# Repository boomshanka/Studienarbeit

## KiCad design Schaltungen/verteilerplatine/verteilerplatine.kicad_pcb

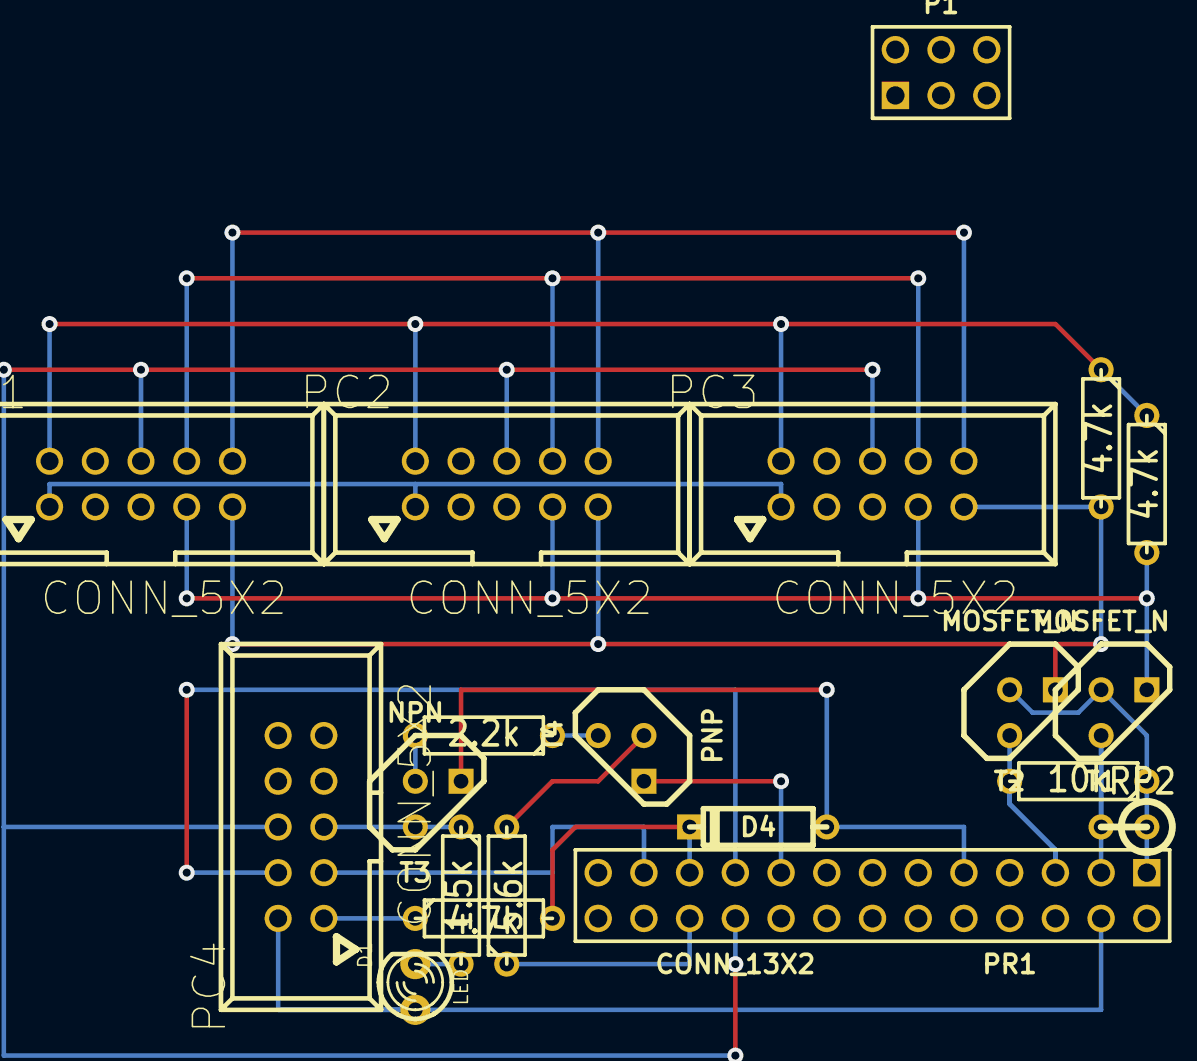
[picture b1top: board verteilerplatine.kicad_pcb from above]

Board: 2 copper layers, 20 parts (0 on the bottom side), 20 nets.

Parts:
D1: LED; LED-3MM
D4: 3.3V; D3
P1: DIN_5; pin_array_3x2
PC1, PC2, PC3, PC4: CONN_5X2; VASCH5x2
PR1: CONN_13X2; pin_array_13x2
R1: 2.2k; R3
R2: 5.6k; R3
R3: 4.7k; R3
RD1: 1.5k; R3
RP1: 10k; R3
RP2: 10k; R1
RP3, RP4: 4.7k; R3
T1, T2: MOSFET_N; TO92DGS
T3: NPN; TO92
T4: PNP; TO92

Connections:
+3.3V: PR1.1, PR1.17, RP1.1, RP2.1, T1.G, T2.G, T4.1
+5V: D1.1, P1.1, PC1.2, PC2.2, PC3.2, PC4.2, PR1.2, PR1.4, RP3.1, RP4.1
+12V: P1.2, PC1.8, PC2.8, PC3.8
-12V: P1.4, PC1.10, PC2.10, PC3.10
/Mikrocontroller/MISO: PC4.1, R3.1
/Mikrocontroller/MOSI: PC4.4, PR1.19
/Mikrocontroller/Reset: PC4.5, RD1.1, T3.3
/Mikrocontroller/SCK: PC4.3, PR1.23
/Mikrocontroller/SCL: PC1.9, PC2.9, PC3.9, RP3.2, T2.D
/Mikrocontroller/SDA: PC1.7, PC2.7, PC3.7, RP4.2, T1.D
/RaspberryPI/MISO: D4.2, PR1.21, R3.2
/RaspberryPI/Reset: PR1.22, R2.1
/RaspberryPI/SCL: PR1.5, RP1.2, T2.S
/RaspberryPI/SDA: PR1.3, RP2.2, T1.S
GND: D4.1, P1.3, PC1.6, PC2.6, PC3.6, PC4.6, PR1.6, PR1.9, PR1.14, PR1.20, PR1.25, T3.1
unnamed: R2.2, T4.2
unnamed: R1.1, T4.3
unnamed: R1.2, T3.2
unnamed: PC1.1, PC2.1, PC3.1
unnamed: D1.2, RD1.2

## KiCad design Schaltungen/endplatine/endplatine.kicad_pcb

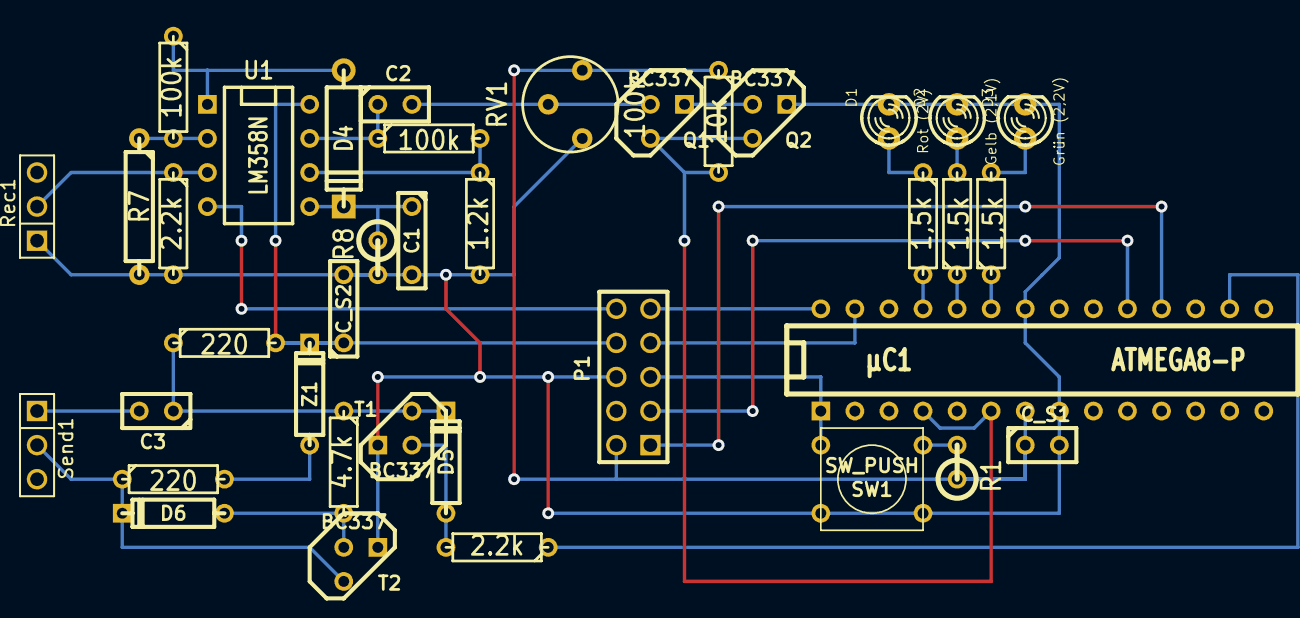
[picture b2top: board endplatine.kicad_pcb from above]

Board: 2 copper layers, 38 parts (0 on the bottom side), 32 nets.

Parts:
C1: 100p; C2
C2: 10n; C1
C3: 100n; C1
C_S1: 100n; C1
C_S2: 100n; C2
D1: Rot (2V); LED-3MM
D2: Gelb (2,1V); LED-3MM
D3: Grün (2,2V); LED-3MM
D4: DIODE; D4
D5, D6: DIODE; D3
P1: CONN_5X2; PIN_ARRAY_5x2
Q1, Q2: BC337; TO92-EBC
R1: 10k; R1
R2, R3, R4: 1,5k; R3
R5: 2.2k; R3
R6, R9: 100k; R3
R7: 1.2k; R4
R8: 560k; R1
R10: 1.2k; R3
R11: 10k; R3
R12, R13: 220; R3
RB1: 2.2k; R3
RB2: 4.7k; R3
RV1: 100k; RV2
Rec1: 2.55nF; PIN_ARRAY_3X1
SW1: SW_PUSH; SW_PUSH_SMALL
Send1: 2,55n; PIN_ARRAY_3X1
T1, T2: BC337; TO92-EBC
U1: LM358N; DIP-8__300
Z1: 3.9V; D3
µC1: ATMEGA8-P; DIP-28__300

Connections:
+5V: C_S1.1, P1.2, R1.1, R11.1, RV1.3, µC1.7
+12V: C_S2.1, P1.8, R12.2, U1.8, Z1.2
-12V: P1.10, U1.4
/Mikrocontroller/Empfänger/Signal: Q1.C, Q2.C, R11.2, µC1.4, µC1.6
/Mikrocontroller/Sender/40kHz PWM: RB1.1, µC1.16
GND: C1.2, C_S1.2, C_S2.2, D1.2, D2.2, D3.2, P1.6, Q2.E, R5.2, R7.2, R8.2, R10.2, RV1.1, Rec1.1, SW1.1, T1.E, T2.E, µC1.8, µC1.22
MISO: P1.1, µC1.18
MOSI: P1.4, µC1.17
unnamed: R3.1, µC1.24
unnamed: R4.2, µC1.25
unnamed: D3.1, R2.2
unnamed: D2.1, R3.2
unnamed: D1.1, R4.1
unnamed: R2.1, µC1.23
unnamed: C3.2, Send1.1
unnamed: R13.2, Z1.1
unnamed: C3.1, D5.2, R12.1, RB2.1, T1.C
unnamed: D5.1, RB1.2, T1.B
unnamed: D6.2, R13.1, Send1.2, T2.C
unnamed: D6.1, RB2.2, T2.B
unnamed: R6.2, R7.1, U1.2
unnamed: D4.1, R6.1, U1.1
unnamed: C2.1, R9.1, U1.7
unnamed: Q1.E, Q2.B
unnamed: R9.2, R10.1, U1.6
unnamed: R5.1, Rec1.2, U1.3
unnamed: C2.2, Q1.B, RV1.2
unnamed: C1.1, D4.2, R8.1, U1.5
Reset: P1.5, R1.2, SW1.2, µC1.1
SCK: P1.3, µC1.19
SCL: P1.9, µC1.28
SDA: P1.7, µC1.27

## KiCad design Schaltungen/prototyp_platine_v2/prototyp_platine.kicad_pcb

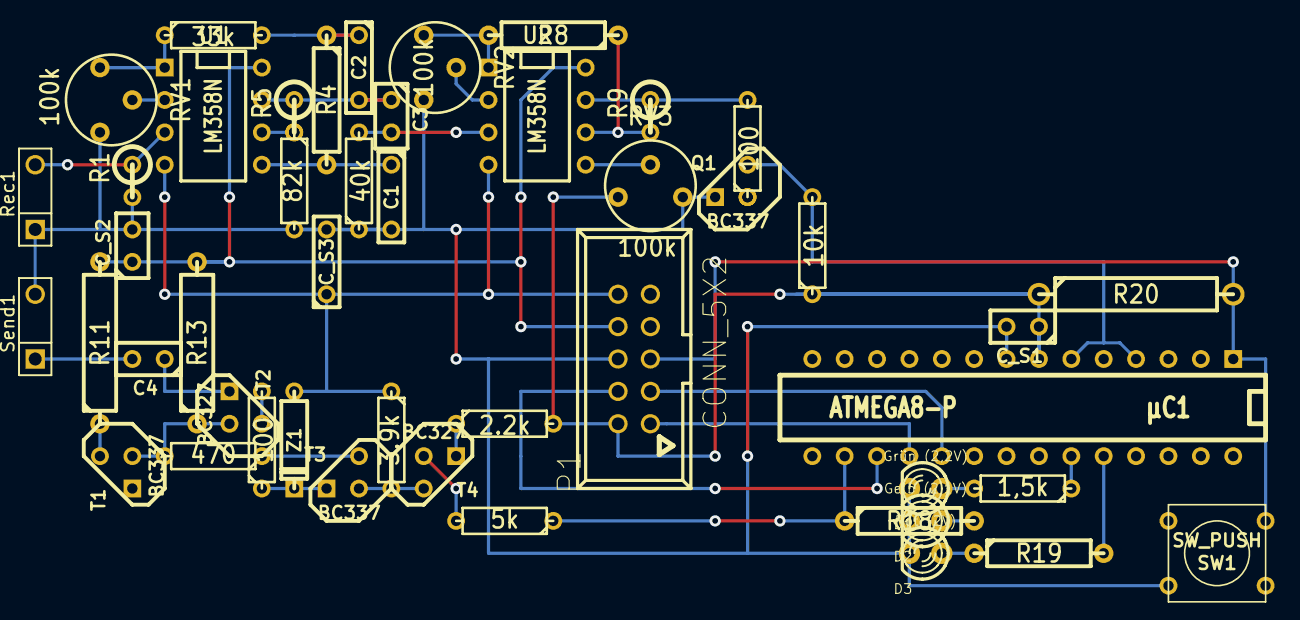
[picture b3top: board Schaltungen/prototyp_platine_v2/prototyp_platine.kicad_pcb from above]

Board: 2 copper layers, 47 parts (0 on the bottom side), 41 nets.

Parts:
C1, C2: 100p; C2
C3: 100p; C1
C4: 100n; C1
C_S1, C_S2: 100n; C1
C_S3: 100n; C2
D1: Grün (2,2V); LED-3MM
D2: Gelb (2,1V); LED-3MM
D3: Rot (2V); LED-3MM
P1: CONN_5X2; VASCH5x2
Q1: BC337; TO92-EBC
R1: 1.8k; R1
R3: 33k; R3
R4: 33k; R4
R5: 33k; R1
R6: 82k; R3
R7: 40k; R3
R8: 10k; R4
R9: 10k; R1
R10: 10k; R3
R11: 100; R5
R12: 100; R3
R13: 10k; R5
R14: 470; R3
R15: 2.2k; R3
R16: 3.9k; R3
R17: 1,5k; R3
R18, R19: 1,5k; R4
R20: 10k; R6
RB1: 100; R3
RB2: 5k; R3
RV1, RV2, RV3: 100k; RV2
Rec1: 2.55nF; PIN_ARRAY_3X1
SW1: SW_PUSH; SW_PUSH_SMALL
Send1: 2,55n; PIN_ARRAY_3X1
T1, T3: BC337; TO92-EBC
T2, T4: BC327; TO92-EBC
U1, U2: LM358N; DIP-8__300
Z1: 3.9V; D3
µC1: ATMEGA8-P; DIP-28__300

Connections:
+5V: C_S1.1, P1.2, R10.1, R15.2, R20.1, RV3.1, µC1.7
+12V: C_S2.1, P1.8, R11.2, R13.2, U1.8, U2.8
-12V: C_S3.1, P1.10, R16.1, U1.4, U2.4, Z1.1
/Mikrocontroller/Empfänger/Signal: Q1.C, R10.2, µC1.4, µC1.6
/Mikrocontroller/Sender/40kHz PWM: R18.1, RB2.1, µC1.16
GND: C1.2, C_S1.2, C_S2.2, C_S3.2, D1.2, D2.2, D3.2, P1.6, Q1.E, R1.2, R6.2, R7.1, RV1.3, RV2.3, RV3.3, Rec1.1, SW1.1, Send1.2, µC1.8
MISO: P1.1, µC1.18
MOSI: P1.4, µC1.17
unnamed: D1.1, R17.2
unnamed: D3.1, R19.1
unnamed: R19.2, µC1.24
unnamed: R17.1, µC1.23
unnamed: D2.1, R18.2
unnamed: C4.1, T1.E, T2.E
unnamed: R14.1, T3.C
unnamed: C4.2, Send1.1
unnamed: R11.1, T1.C
unnamed: R12.1, T3.E, Z1.2
unnamed: R12.2, T2.C
unnamed: R13.1, R14.2, T1.B, T2.B
unnamed: RB2.2, T4.B
unnamed: R15.1, T4.E
unnamed: R16.2, T3.B, T4.C
unnamed: C3.2, R7.2, U2.3
unnamed: R8.2, RV2.1, U2.1
unnamed: RV2.2, U2.2
unnamed: C2.2, C3.1, R5.1, U1.7
unnamed: R9.1, RB1.2, U2.7
unnamed: RV3.2, U2.5
unnamed: R8.1, R9.2, U2.6
unnamed: R5.2, R6.1, U1.6
unnamed: C2.1, R3.2, R4.1
unnamed: C1.1, R4.2, U1.5
unnamed: R1.1, Rec1.2, U1.3
unnamed: Q1.B, RB1.1
unnamed: R3.1, RV1.1, U1.1
unnamed: RV1.2, U1.2
Reset: P1.5, R20.2, SW1.2, µC1.1
SCK: P1.3, µC1.19
SCL: P1.9, µC1.28
SDA: P1.7, µC1.27

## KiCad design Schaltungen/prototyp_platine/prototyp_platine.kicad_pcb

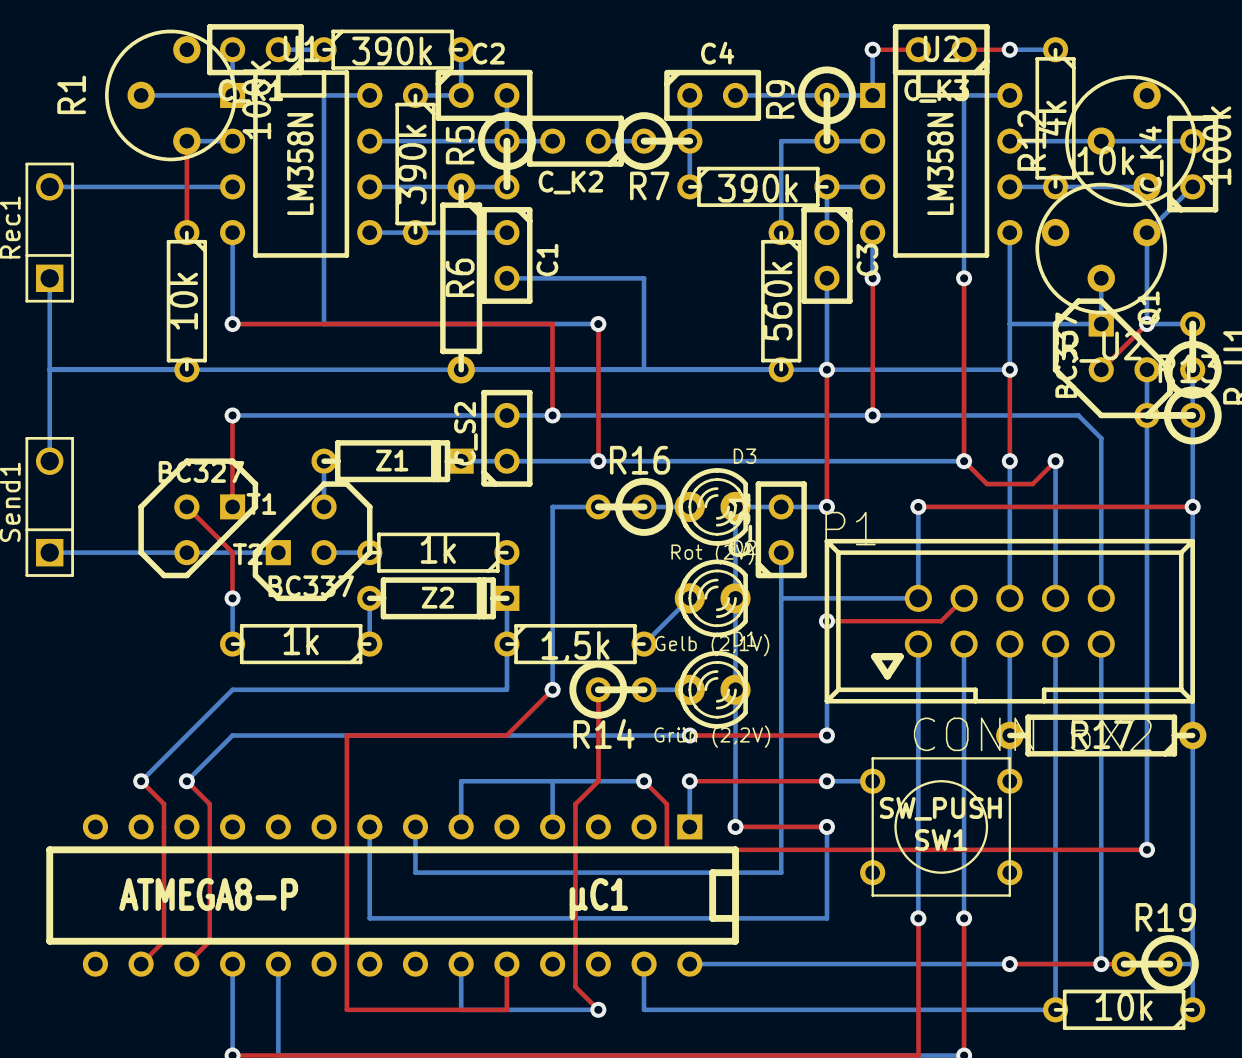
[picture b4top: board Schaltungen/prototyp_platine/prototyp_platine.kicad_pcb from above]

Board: 2 copper layers, 48 parts (0 on the bottom side), 39 nets.

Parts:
C1, C2, C3, C4: 10p; C1
C_K1, C_K2: 10p; C1
C_K3: 1n; C1
C_K4: >500p, 100n; C1
C_S1, C_S2: 100n; C1
D1: Grün (2,2V); LED-3MM
D2: Gelb (2,1V); LED-3MM
D3: Rot (2V); LED-3MM
P1: CONN_5X2; VASCH5x2
Q1: BC337; TO92-EBC
R1, R12: 100k; RV2
R2, R18: 10k; R3
R3, R4, R8: 390k; R3
R5, R9: 330k; R1
R6: 560k; R4
R7: 390k; R1
R10: 560k; R3
R11: 4k; R3
R13, R19: 10k; R1
R14, R16: 1,5k; R1
R15: 1,5k; R3
R17: 10k; R4
R_B1, R_B2: 1k; R3
R_U1: 47k; R1
R_U2: 10k; RV2
Rec1: Empfänger; PIN_ARRAY_3X1
SW1: SW_PUSH; SW_PUSH_SMALL
Send1: 2,55n; PIN_ARRAY_3X1
T1: BC337; TO92-EBC
T2: BC327; TO92-EBC
U1, U2: LM358N; DIP-8__300
Z1: 4V; D3
Z2: 12V; D3
µC1: ATMEGA8-P; DIP-28__300

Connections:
+5V: C_S1.1, P1.2, R13.1, R17.1, R18.1, R19.1, R_U1.1, µC1.7
+12V: C_S2.1, P1.8, U1.8, U2.8, Z1.2
-12V: C_S2.2, P1.10, T2.E, U1.4, U2.4
/Empfänger/Signal: Q1.C, R13.2, µC1.4, µC1.6
/Mikrocontroller/40kHz PWM: R15.1, R_B1.1, Z2.2, µC1.16
GND: C1.2, C3.2, C_S1.2, D1.2, D2.2, D3.2, P1.6, Q1.E, R2.2, R6.2, R10.2, R_U2.2, Rec1.1, SW1.1, Send1.2, U2.5, µC1.8
MISO: P1.1, µC1.18
MOSI: P1.4, µC1.17
unnamed: D3.1, R16.1
unnamed: D1.1, R14.2
unnamed: R16.2, µC1.24
unnamed: R14.1, µC1.23
unnamed: D2.1, R15.2
unnamed: Send1.1, T1.E, T2.C
unnamed: R_B1.2, T1.B
unnamed: T1.C, Z1.1
unnamed: R_B2.2, T2.B
unnamed: R_B2.1, Z2.1
unnamed: C_K1.2, R1.2, U1.1
unnamed: R1.1, R2.1, U1.2
unnamed: Rec1.2, U1.3
unnamed: C_K3.1, R11.1
unnamed: R11.2, R12.1, U2.6
unnamed: C_K1.1, R3.1
unnamed: C4.2, C_K3.2, R9.1, U2.1
unnamed: C_K2.1, R7.1
unnamed: C2.2, C_K2.2, R5.1, U1.7
unnamed: C_K4.2, R12.2, U2.7
unnamed: C_K4.1, Q1.B, R_U1.2, R_U2.1
unnamed: R9.2, R10.1, U2.2
unnamed: R5.2, R6.1, U1.6
unnamed: C2.1, R3.2, R4.1
unnamed: C1.1, R4.2, U1.5
unnamed: C3.1, R8.2, U2.3
unnamed: C4.1, R7.2, R8.1
Reset: P1.5, R17.2, SW1.2, µC1.1
SCK: P1.3, µC1.19
SCL: P1.9, R19.2, µC1.28
SDA: P1.7, R18.2, µC1.27

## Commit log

2014-11-25 .gitignore für C-Code erweitert
2014-11-25 Vorlage für TeX-Dokumentation hinzugefügt.
2014-11-25 Makefile für AVR hinzugefügt.
2014-12-01 Entwurf von Schaltplan für Senderverstärker hinzugefügt.
2014-12-02 Datenblatt und Pinbelegung von ATmega8 und Pinbelegung von GPIO-Interface hinzugefügt.
2014-12-03 Erster Code für Firmware hinzugefügt, 40kHz-Signal wird per FastPWM erzeugt.
2014-12-04 Mehr Datenblätter.
2014-12-25 Sourcecode für Two-Wire-Interface (I²C) hinzugefügt.
2014-12-26 Grobe Strukturierung der Dokumentation.
2014-12-26 Dokument >Operationsverstärker in der Praxis< zur Entwicklung von Filterschaltungen hinzugefügt.
2015-01-02 Sender-Schaltungen (12V und 20V) hinzugefügt. Programm zum öffnen: EAGLE (http://www.cadsoft.de/eagle-pcb-design-software/)
2015-01-02 Aktive Filter (HP & TP) für die Empfängerschaltung hinzugefügt.
2015-01-03 TWI-Modul aufgeteilt in Master und Slave. Master-Modul wird wahrscheinlich nicht benötigt, da bisher R-PI einziger Master auf dem Bus ist.
2015-01-03 Bilder von Oszi (incl Beschreibung) des letzten Labortermins hinzugefügt.
2015-01-09 Vollständiger Schaltplan für Prototyp-Platine hinzugefügt. Softwareumstieg von EAGLE->KiCAD ( http://www.kicad-pcb.org/ ). .gitignore erweitert.
2015-01-09 Berechnung des aktiven Tiefpassfilters, verbaut auf Prototyp-Platine. Öffnen mit Programm: AktivFilter 3.2 ( http://www.aktivfilter.de/ ).
2015-01-09 Kleinere Änderungen am Schaltplan, Footprint-Liste hinzugefügt.
2015-01-11 Platinenentwurf fertig.
2015-01-15 Firmware-Code erweitert, einige Tests.
2015-01-15 Dateien vergessen..
2015-01-22 Schaltungen (Sender & Empfänger, unvollständig) für Simulation hinzugefügt. Programm für Simulation: LTspice IV
2015-01-22 Bilder von Simulationen für Doku hinzugefügt
2015-01-23 Empfänger-Schaltung nach ursprünglicher Idee vollständig (allerdings nur eine Filterstufe) und funktioniert. Einige Änderungen sind aber noch sinnvoll.
2015-01-23 Invertierenden Verstärker in Nicht-invertierenden Verstärker mit (neg.) Offset umgewandelt -> Entkopplung des Transistors mit Kondensator ist nicht mehr nötig, Signal wird dadurch präziser.
2015-01-23 Bild von gesamter Schaltung mit Veranschaulichung von Offset hinzugefügt.
2015-01-26 Schaltung "sender.asc": Ganz simple Sendeschaltung mit einem Transistor und 17V U_ss. Laden über R, dauerhafter Stromfluss bei Signal. Schaltung "sender_push_pull.asc": Aufwendige Schaltung mit Push-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
2015-01-27 Sender Push-Pull komplett überarbeitet. Funktioniert jetzt mit zwei NPN in der Endstufe.
2015-01-29 Latex-Vorlage durch neuere Version ersetzt.
2015-01-29 Empfängerschaltung aktualisiert: Invertierender Verstärker an erster Stelle wg nötigen Eingangswiderstand für Hochpass zwischen Verstärker und Empfänger.
2015-02-04 Doku: -Kapitel Schaltungen->Entwicklung. Soll allgemein die Entwicklung von Schaltungen und Software, sowie Architektur der Lösung behandeln -Kapitel für Sender und Empfänger hinzugefügt -Kapitel für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
2015-02-04 Content!
2015-02-05 Weiter an der Doku gearbeitet. Sender mit Komparatorschaltung erklärt.
2015-02-06 Doku komplett umstrukturiert. Möglicherweise können Kapitel von Sender und Empfänger noch zusammengefasst werden.
2015-02-09 Weitere Push-Pull-Schaltung hinzugefügt. Verwendet NPN und PNP in Endstufe, dadurch wird kurzzeitiges gleichzeitiges Öffnen vermieden. -> Es fließt weniger Strom, Spannungsquelle wird nicht unnötig b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
2015-02-10 2. Kapitel Projektübersicht weiter geschrieben. Übersicht, Architektur und einzelne Komponenten beschrieben.
2015-02-11 TikZ-Bild für Architekturschema zur Doku hinzugefügt.
2015-02-16 Bild von Komparatorschaltung hinzugefügt.
2015-02-17 FINALLY! Gegentakt-Ausgangsstufe mit MOSFETS umgesetzt. Funktioniert perfekt.
2015-02-17 Datei für Adressen von Internetquellen hinzugefügt.
2015-02-18 Sender (Bipolar) V1 überarbeitet und V2 rausgeschmissen. Ist nun als Alternativlösung zu MOSFET-Ansatz denkbar.
2015-02-18 Bild von OP-Simulation für Komparatorschaltung hinzugefügt.
2015-02-18 Kapitel 3 (Sender) und 4 (Empfänger) in neues Kapitel Schaltungen verschoben.
2015-02-18 Kapitel Schaltungen weiter geschrieben. Transistorschaltungen angefangen.
2015-02-19 Bild von Transistorschaltungen hinzugefügt.
2015-02-19 (Mal wieder) kleine Korrektur an Gegentakt-Sendeschaltung.
2015-02-19 Kapitel Senderschaltung weiter geschrieben. Transistor-Teil und Einleitung vorerst fertig, Gegentaktstufe in Arbeit.
2015-02-20 Bezeichnungen auf Bild von Transistoren geändert
2015-02-20 Schaltung für Verteilerplatine hinzugefügt. Signalwandlung für SPI von 3.3V (RPI) -> 5V (AVR) noch notwendig. Websitequellen geupdated.
2015-02-22 Schaltplan und Platinenentwurf von Verteilerplatine fertig.
2015-03-10 Merge
2015-03-11 Anpassung widerstandswerte an E12-Reihe (wie in Testschaltung)
2015-03-18 Layout für überarbeitete Prototyp-Platine fast fertig.
2015-03-19 Prototyp-Platine..
2015-03-21 Schema fertig.
2015-04-01 Kleine Änderungen am Schaltplan und Layout. Firmware: Dateien für Display (7-Segment Anzeige) hinzugefügt.
2015-04-01 Oszibilder (Verstärker) von heute hinzugefügt.
2015-04-16 Update von Firmware und Schaltungen.
2015-04-16 Fotos von heute aus dem Labor hinzugefügt.
2015-04-30 Firmware update
2015-05-04 Erster Entwurf von Endplatine hinzugefügt.
2015-05-04 Reihenfolge geändert..
2015-05-07 Empfängerschaltung vervollständigt. Tests wurden vertagt.
2015-05-11 Schaltung für Endplatine fertig. Makefile für neuen Programmer angepasst.
2015-05-12 Platinenentwurf für Endplatine hinzugefügt und fertig gestellt.
2015-05-13 Firmware für Endplatine angefangen, kleine Änderungen am Platinenentwurf.
2015-05-13 Removed files, .gitignore updated.
2015-05-15 Firmware update, Transistor in Schaltung geändert.
2015-05-15 platinenlayout an überarbeiteten Verstärker angepasst. Wenn das nicht klappt -> Extra TreiberIC o.ä.
2015-05-18 Kleine Änderungen am Code
2015-06-03 Update der Doku. Bild der Gegentaktstufe hinzugefügt.
2015-06-04 TWI-Code in main angepasst. Sollte irgendwie so funktionieren..
2015-06-08 Doku update
2015-06-08 Doku-Update von Marina.
2015-06-08 Firmware update.
2015-06-09 Doku und Windmühlen.
2015-06-11 Kontrast von OP-Signalverlauf-Bild erhöht.
2015-06-11 Firmware: Main überarbeitet, unterscheidung der Platinen in Software möglich, Pulsierende LEDs per SoftPWM.
2015-06-11 Protokoll-Header hinzugefügt.
2015-06-12 Doku: Deckblatt angebasst, Teil über Sender fertig gestellt.
2015-06-12 Oszi-Bilder aus dem Labor + Beschreibung hinzugefügt.
2015-06-12 Bild gedreht.
2015-06-12 Doku-Update: Firmware mit einzelnen Komponenten beschrieben, Berechnungen für Genauigkeit und Reichweite. Kapitel über Schaltungen (Sender) bearbeitet.
2015-06-12 Time of Flight Interface neu geschrieben, Logik in Main überarbeitet. Unvollständig und verbuggt.
2015-06-12 Bugs gefixt, code überarbeitet.
2015-06-13 Stand Firmware vor neuem TWI-Code.
2015-06-13 TWI funktioniert! Neue lib eingesetzt, Empfangen und Senden per Interrupt.
2015-06-13 Abstandsmessung zwischen den Sensoren nun möglich.
2015-06-14 Kleine Firmwareänderung: Controller beendet Zustand Warten (bei Abstandsmessung untereinander), wenn Kommando Connect/Disconnect gesendet wird.
2015-06-15 Doku: Vergessenes Bild hinzugefügt. Firmware: Genauigkeit durch exakte Schallgeschwindigkeit verbessert. Casts müssen noch untersucht werden.
2015-06-15 Alternative Berechnung des Abstands ohne Gleitkommazahlen.
2015-06-15 Doku: Kapitel über Platinen angefangen. Dafür fehlen noch einige Bilder & Details.
2015-06-15 Änderungen am Code rückgängig gemacht: Takt ist so ungenau, dass exakte Schallgeschwindigkeit die Genauigkeit eher verschlechtert.
2015-06-16 Doku von Marina.
2015-06-20 Firmware überarbeitet, I2C-Bug gefixt und an Raspberry-Pi angepasst (Bit 8 wird durch Bug im Chip abgeschnitten).
2015-06-22 Newline bei Description
2015-06-22 Doku. Kapitel 2 überarbeitet, Text von Christian hinzugefügt.
2015-06-22 Transformierte Oszi-Bilder hinzugefügt.
2015-06-23 Bilder von Christian hinzugefügt. Kapitel Inbetriebnahme hinzugefügt (ohne Inhalt)
2015-06-23 Kohle Kohle, Kooohle äääh Doku Doku Doku..!
2015-07-03 Doku: Empfängerschaltungen
2015-07-05 Verbesserungen an Doku
2015-07-05 Beschriftung der Oszi-Bilder
2015-07-05 Marinas Doku.
2015-07-05 Kapitel Platine fertig, Bilder hinzugefügt.
2015-07-06 Letzen Änderungen an der Doku. Quellen, Text, Bode-Diagramm und Firmware-Ablaufdiagramm.
2015-07-06 Anpassung der Verteiler-Platine (Verbindung der Trigger-Leitung)
2015-07-07 Kleine Korrekturen an der Doku (Rechtschreibung, Referenze, Formel)
